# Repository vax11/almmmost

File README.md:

# Almmmost

Almmmost is a reimplementation of TeleVideo, Inc's MmmOST network operating
system, which provided a small business network to a set of Z80 or 8088-based
TeleVideo computers in the early 1980s.

Almmmost reimplements the core functions of file and disk sharing, along with
"special file" handling, which allows programs to interact with the server to
request dynamic data, or data from other sources.

The hardware part of Almmmost depends on a Next Thing Co. CHIP single board
computer, and a custom GPIO interface to a Zilog Z85C30 serial chip. This
provides an RS-422 SDLC interface running at 800K baud, for the client systems
to talk to.  A custom Linux kernel driver is provided to interface with the 
hardware, and allow easy porting to other similar single-board computers.

The kernel driver is in the "tvi\_sdlc" directory, and depends on kernel
sources to be built. If building on a NTC Chip, I recommend getting a copy
of the 4.4.138-chip kernel from here: 
https://github.com/kaplan2539/CHIP-Debian-Kernel

The needed dtb to enable the PWM, which provides the serial Tx clock, is
provided as well, and should be copied to /boot/sun5i-r8-chip.dtb

libini is required, and can be acquired from here:
https://github.com/pcercuei/libini

To compile libini, run "cmake ." in the source directory, and then the usual
make / make install.  On Debian, you'll probably first need to edit 
CMakeLists.txt to change the required cmake version to 3.0.0. I had no issues
with changing that requirement in my testing.

To build Almmmost, once you have the other things built, just cd into the 
directory and run "make".  There are a set of Z80 programs that can be built
with "z80asm" from the like named Debian/Ubuntu package.  To copy files onto
the client, you can point the "filein.sys" link to the file on the server,
and on the client just do:
```
pip a:whatever.com=b:filein.sys
```

Almmmost requires OS images for the client systems. The stock config file 
uses MmmOST 2.1 versions of the client OSes.  These are available in the
TS806 install images "tv806.zip" on Dave Dunfield's site, which will need
to be extracted from the Imagedisk images. You can use Imagedisk to convert
to a raw image, and then 22DISK, UNIFORM, or simlilar to copy the files
out. The OS images are named like "USERCPM.DAT":
http://www.classiccmp.org/dunfield/img/index.htm

To generate the binary versions of the bootloaders, you can convert the HEX
version to a binary version, doing something like this, on linux:
```
objcopy -i ihex -o binary XPDUBOOT.HEX XPDUBOOT.BIN
```

You'll next need to generate disk images. CP/M expects empty disks to
contain all e5 (hex) bytes, so I've included a program, "make\_e5.c", which
generates a stream of e5 bytes. For an 8MB image, do:
```
./make_e5 | dd of=drive_a.img bs=1M count=8
```

For floppy disk images, you can use Imagedisk images converted to raw images
on DOS:
```
IMDU /BIN BLAH.IMD BLAH.BIN
```

Running almmmost is as simple as:
```
./almmmost almmmost.ini
```

## Configuration file
almmmost.ini is an ini-format config file to set most of the parameters for
Almmmost.  A lot of it won't need to be touched to make this work, but here's
the main things you may want to modify:

```
[Device]
```
Set Ports= to the number of ports you have, and for each one (numbered 0 and up),
have a User Dev n = line pointing to the device name, and a User Port n = line
with the number of the ports on the card.  Each Z85C30 card has two ports, and
are numbered based on the board number * 2. So a board with the dip switches
set for the first select, would be ports 0 (A) and 1 (B). The second select is
ports 2 (A) and 3 (B).

```
[General]
```
This sets the MmmOST general revisison number and the disk number (0=A) for the
print spool.  Print spooling is not yet implemented.

```
[Port n]
```
This sets whether or not the client on this port number (these are based on the
numbers you set in the device section, not the physical numbers) runs an 
autologon command, and which private directory number it should use for its 
private drive.

```
[Clients]
```
This sets where the OS images and bootloaders are kept on the disk, and the
max number for the hardware type

```
[Client OSTYPE n]
```
This sets the filenames for the boot loader and OS image for each Client's 
hardware type.  This is the hardware type sent by the Boot rom to the server, 
and generally is:

```
0 = U = TS-800A, TS-801, TS-802
1 = TS-802H
2 = TS-1602
3 = TS-1603
4 = TS-803
5 = TS-803H
6 = TS-800R
7 = TPC-I
```

Values are listed for the base address that byte 0 of the OS image is loaded at,
the memory address for the Hardware Parameter Table (HPAM), and the address
of the Console Buffer (CONBUF). These are somewhat documented in almmmost\_osload.h

```
[Disks] 
```
This lists the number of drives that are presented to the client, and the
directory that they're stored in, along with the maximum private directory number

```
[Disk n]
```
This gives the disk type, image file names/rw status, and parameters for CP/M:
```
Type : either PRIVATE, PUBLIC, or PUBLIC_ONLY, matching MmmOST's definitions.
Image n : one Image is used per private directory on a disk. 0 is used for
	public/public only disks
Floppy : Y or N depending on if it's emulating a floppy disk that can be changed
SPT : CP/M Sectors per track
BSF : CP/M Block shift factor
DBM : CP/M Max data block number
DBL : Maximum directory entry number
ALx : The number of blocks reserved for the directory entries. This matches the
	number of 1 bits in AL0 / AL1
RES : The number of reserved tracks (for OS or disk partitioning)
EXM : CP/M Extent Mask
```

Most of those values are based on the CP/M Disk Paramaeter Block information to
describe a disk image. The example config gives A: as a private drive of 8MB 
(the max in CP/M 2.2), B: as a public (shared file) drive of 8MB, and C: matching
the TeleVideo 360K CP/M floppy format.

## Command interface

Pressing ^C while running will halt the server and bring up a command line,
with commands available for debugging problems, or making some changes to the
system state.  The commands are listed below:

```
abort
```

Abort the current command, useful if Almmmost is waiting for the client to 
send data, but the client is hung up for some reason.

```
locate
```
Prints out the current do/while loop that the server is in, waiting for the
client to do something.

```
reopen <Disk>[:DIR] <filename>
```

eg, reopen C /root/floppy2.img ... or reopen A:0 driveA-dir0.img
Closes the current image file, and opens a new one in its place.  You will 
want to hit ^C on the client after doing this, or it might corrupt the new 
disk.

If filename starts with a "/", it assumes an absolute path, otherwise it 
looks starting in the directory specified in the config file.

```
filein <filename>
```
Changes what file on the server is used to supply data for the "filein.sys"
special file

```
fileout <filename>
```
Changes what file on the server is written to by wiriting to the "fileout.sys"
special file.

```
closeport <n>
```
Closes all open files on port #n.  Useful if the client died, and left files
open. Ensures that data is written back to disk.

```
printfil
```
Print all open files on shared drives

```
printspe
```
Print names of all special files that are handled by Almmmost

```
printdpb
```
Print the CP/M Drive Parameter Blocks that were generated by Almmmost for the
disk images.

```
printhpb
```
Print the Hardware Parameter Blocks that were generated by Almmmost based on
the config file values, for each hardware type

```
saveos <filename>
```
Saves the modified OS image, with the generated HPB/DPH/DPBs that were inserted
into it

```
sync
```
Save all open files on shared drives to the image in their current state 
(makes sure directory entries are saved)

```
exit
quit
```
Runs "sync", and then exits Almmmost.

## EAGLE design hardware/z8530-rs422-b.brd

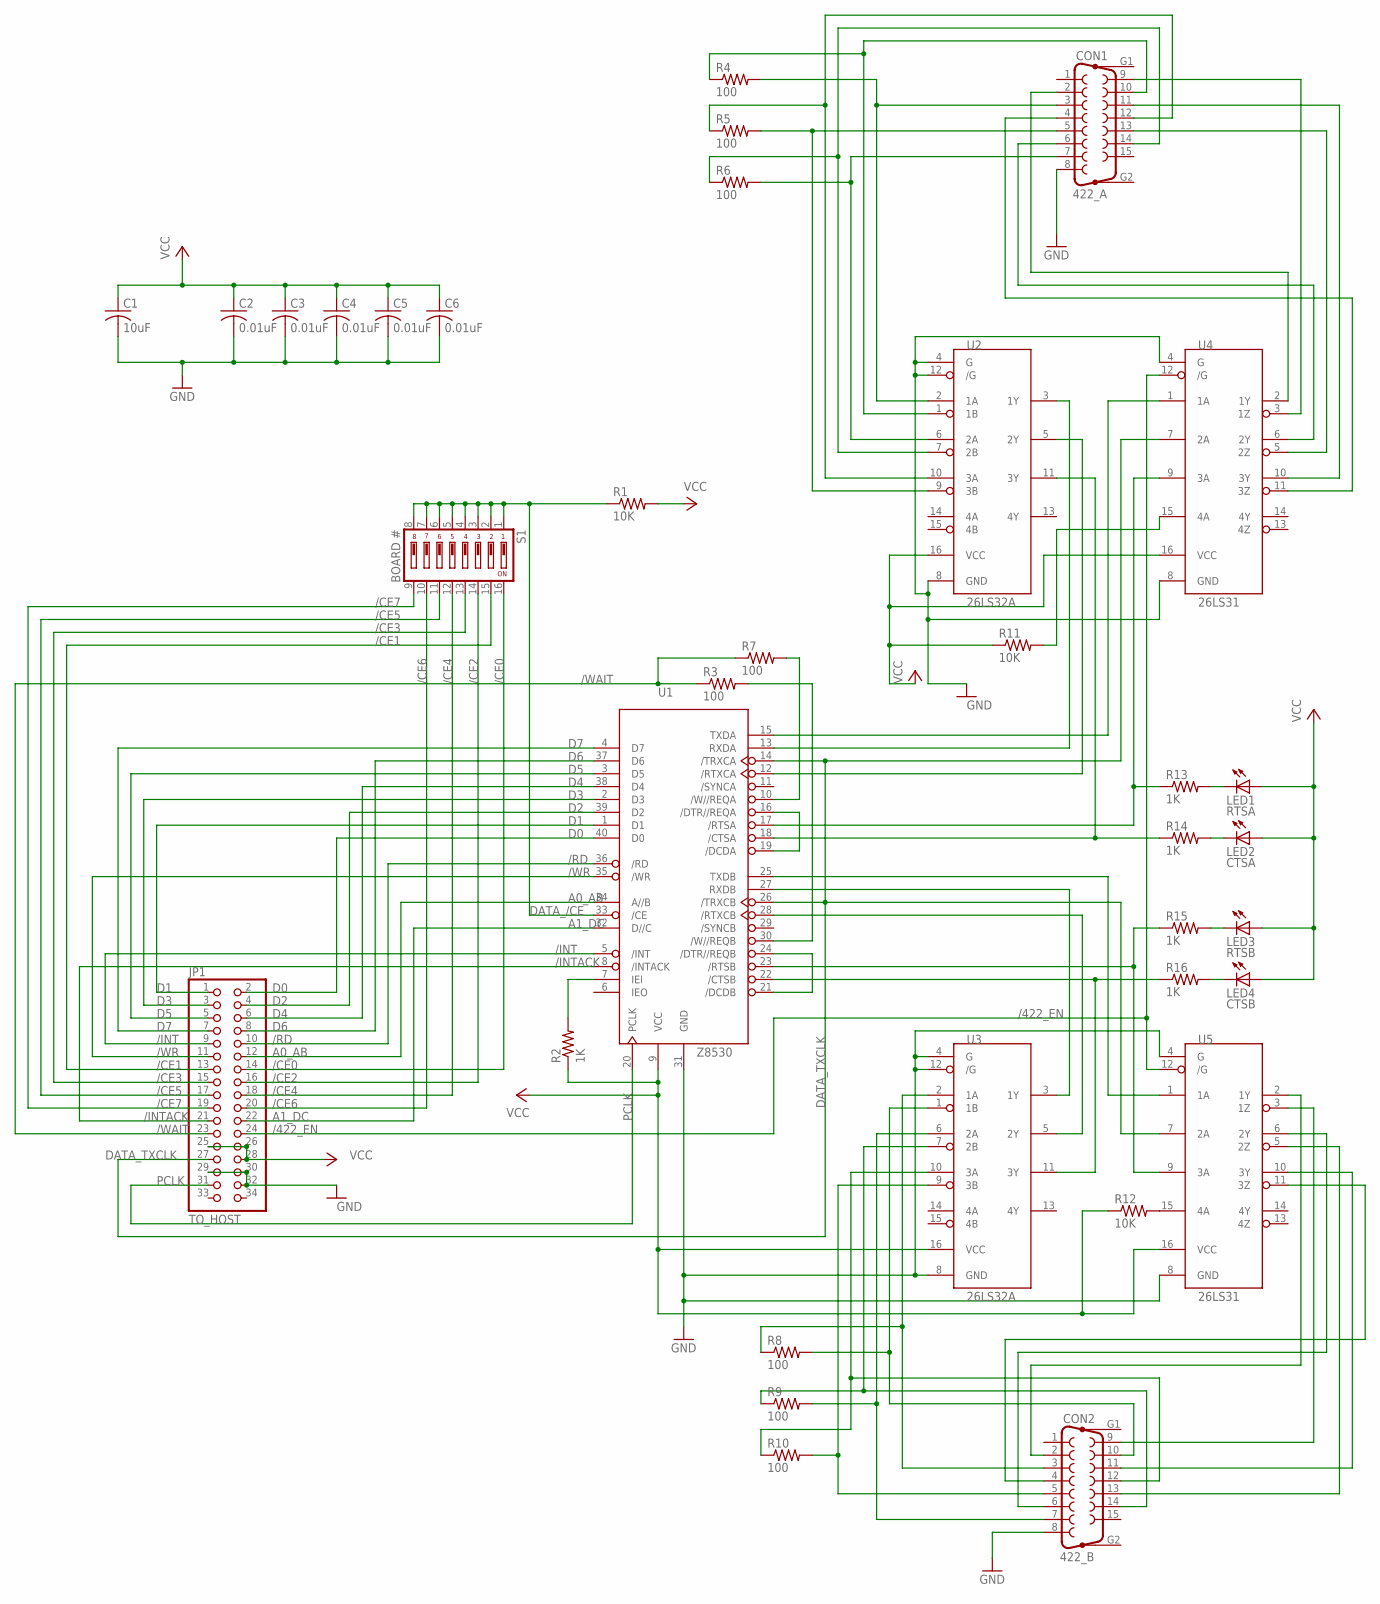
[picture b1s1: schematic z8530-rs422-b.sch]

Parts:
C1: 10uF; C0805
C2, C3, C4, C5, C6: 0.01uF; C0805
CON1: 422_A; F15VP
CON2: 422_B; F15VP
JP1: TO_HOST; 2X17
LED1: RTSA; LED3MM
LED2: CTSA; LED3MM
LED3: RTSB; LED3MM
LED4: CTSB; LED3MM
R1, R11, R12: 10K; R0805
R2, R13, R14, R15, R16: 1K; R0805
R3, R4, R5, R6, R7, R8, R9, R10: 100; R0805
S1: BOARD #; DP-08
U1: Z8530; DIL40
U2, U3: 26LS32A; DIP16
U4, U5: 26LS31; DIP16

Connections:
/422_EN: JP1.24, U4.12 (/G), U5.12 (/G)
/CE0: JP1.14, S1.16
/CE1: JP1.13, S1.15
/CE2: JP1.16, S1.14
/CE3: JP1.15, S1.13
/CE4: JP1.18, S1.12
/CE5: JP1.17, S1.11
/CE6: JP1.20, S1.10
/CE7: JP1.19, S1.9
/INT: JP1.9, U1.5 (/INT)
/INTACK: JP1.21, U1.8 (/INTACK)
/RD: JP1.10, U1.36 (/RD)
/WAIT: JP1.23, R3.1, R7.1
/WR: JP1.11, U1.35 (/WR)
A0_AB: JP1.12, U1.34 (A//B)
A1_DC: JP1.22, U1.32 (D//C)
D0: JP1.2, U1.40 (D0)
D1: JP1.1, U1.1 (D1)
D2: JP1.4, U1.39 (D2)
D3: JP1.3, U1.2 (D3)
D4: JP1.6, U1.38 (D4)
D5: JP1.5, U1.3 (D5)
D6: JP1.8, U1.37 (D6)
D7: JP1.7, U1.4 (D7)
DATA_/CE: R1.1, S1.1, S1.2, S1.3, S1.4, S1.5, S1.6, S1.7, S1.8, U1.33 (/CE)
DATA_TXCLK: JP1.27, U1.14 (/TRXCA), U1.26 (/TRXCB), U4.7 (2A), U5.7 (2A)
GND: C1.2, C2.2, C3.2, C4.2, C5.2, C6.2, CON1.8, CON2.8, JP1.29, JP1.30, JP1.32, U1.31 (GND), U2.4 (G), U2.8 (GND), U2.12 (/G), U3.4 (G), U3.8 (GND), U3.12 (/G), U4.4 (G), U4.8 (GND), U5.4 (G), U5.8 (GND)
unnamed: R7.2, U1.10 (/W//REQA)
unnamed: R3.2, U1.30 (/W//REQB)
unnamed: U1.13 (RXDA), U2.3 (1Y)
unnamed: U1.12 (/RTXCA), U2.5 (2Y)
unnamed: R14.1, U1.18 (/CTSA), U2.11 (3Y)
unnamed: U1.15 (TXDA), U4.1 (1A)
unnamed: R13.1, U1.17 (/RTSA), U4.9 (3A)
unnamed: U1.16 (/DTR//REQA), U1.19 (/DCDA)
unnamed: U1.21 (/DCDB), U1.24 (/DTR//REQB)
unnamed: U1.27 (RXDB), U3.3 (1Y)
unnamed: U1.28 (/RTXCB), U3.5 (2Y)
unnamed: R16.1, U1.22 (/CTSB), U3.11 (3Y)
unnamed: U1.25 (TXDB), U5.1 (1A)
unnamed: R15.1, U1.23 (/RTSB), U5.9 (3A)
unnamed: CON1.3, R4.2, U2.2 (1A)
unnamed: CON1.10, R4.1, U2.1 (1B)
unnamed: CON1.7, R6.2, U2.6 (2A)
unnamed: CON1.14, R6.1, U2.7 (2B)
unnamed: CON1.12, R5.1, U2.10 (3A)
unnamed: CON1.5, R5.2, U2.9 (3B)
unnamed: CON1.2, U4.2 (1Y)
unnamed: CON1.9, U4.3 (1Z)
unnamed: CON1.6, U4.6 (2Y)
unnamed: CON1.13, U4.5 (2Z)
unnamed: CON1.11, U4.10 (3Y)
unnamed: CON1.4, U4.11 (3Z)
unnamed: CON2.3, R8.1, U3.2 (1A)
unnamed: CON2.10, R8.2, U3.1 (1B)
unnamed: CON2.7, R9.2, U3.6 (2A)
unnamed: CON2.14, R9.1, U3.7 (2B)
unnamed: CON2.12, R10.1, U3.10 (3A)
unnamed: CON2.5, R10.2, U3.9 (3B)
unnamed: CON2.2, U5.2 (1Y)
unnamed: CON2.9, U5.3 (1Z)
unnamed: CON2.6, U5.6 (2Y)
unnamed: CON2.13, U5.5 (2Z)
unnamed: CON2.11, U5.10 (3Y)
unnamed: CON2.4, U5.11 (3Z)
unnamed: LED1.K (C), R13.2
unnamed: LED3.K (C), R15.2
unnamed: LED2.K (C), R14.2
unnamed: LED4.K (C), R16.2
unnamed: R2.2, U1.7 (IEI)
unnamed: R11.2, U4.15 (4A)
unnamed: R12.2, U5.15 (4A)
PCLK: JP1.31, U1.20 (PCLK)
VCC: C1.1, C2.1, C3.1, C4.1, C5.1, C6.1, JP1.25, JP1.26, JP1.28, LED1.A, LED2.A, LED3.A, LED4.A, R1.2, R2.1, R11.1, R12.1, U1.9 (VCC), U2.16 (VCC), U3.16 (VCC), U4.16 (VCC), U5.16 (VCC)

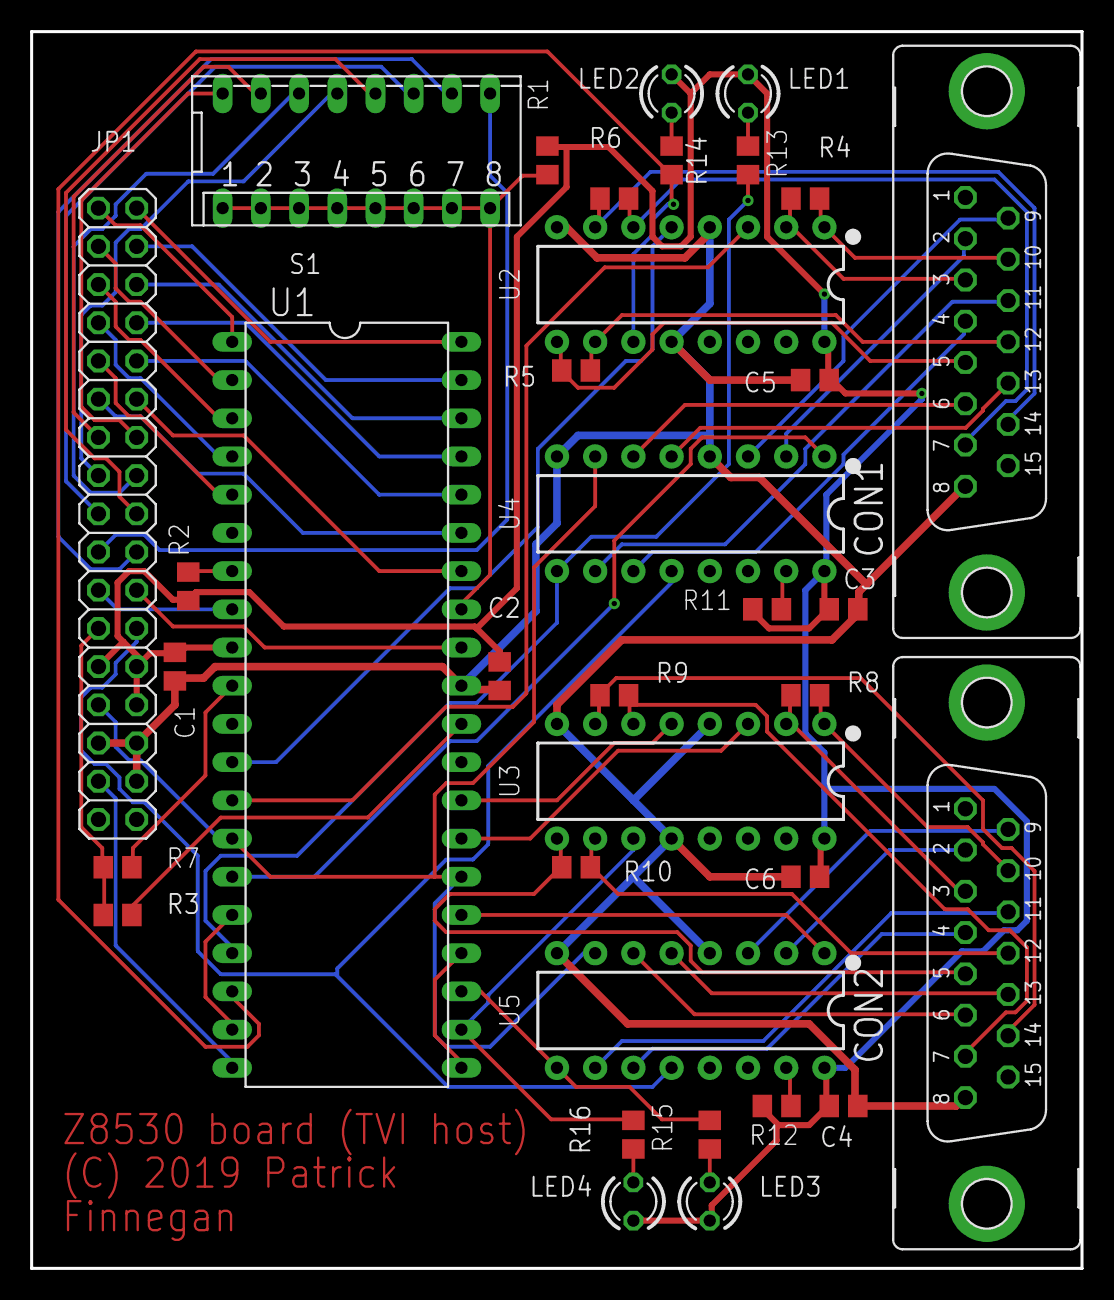
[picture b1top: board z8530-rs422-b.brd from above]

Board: 2 copper layers, 69.8 x 82.2 mm, 35 parts (0 on the bottom side), 74 nets.

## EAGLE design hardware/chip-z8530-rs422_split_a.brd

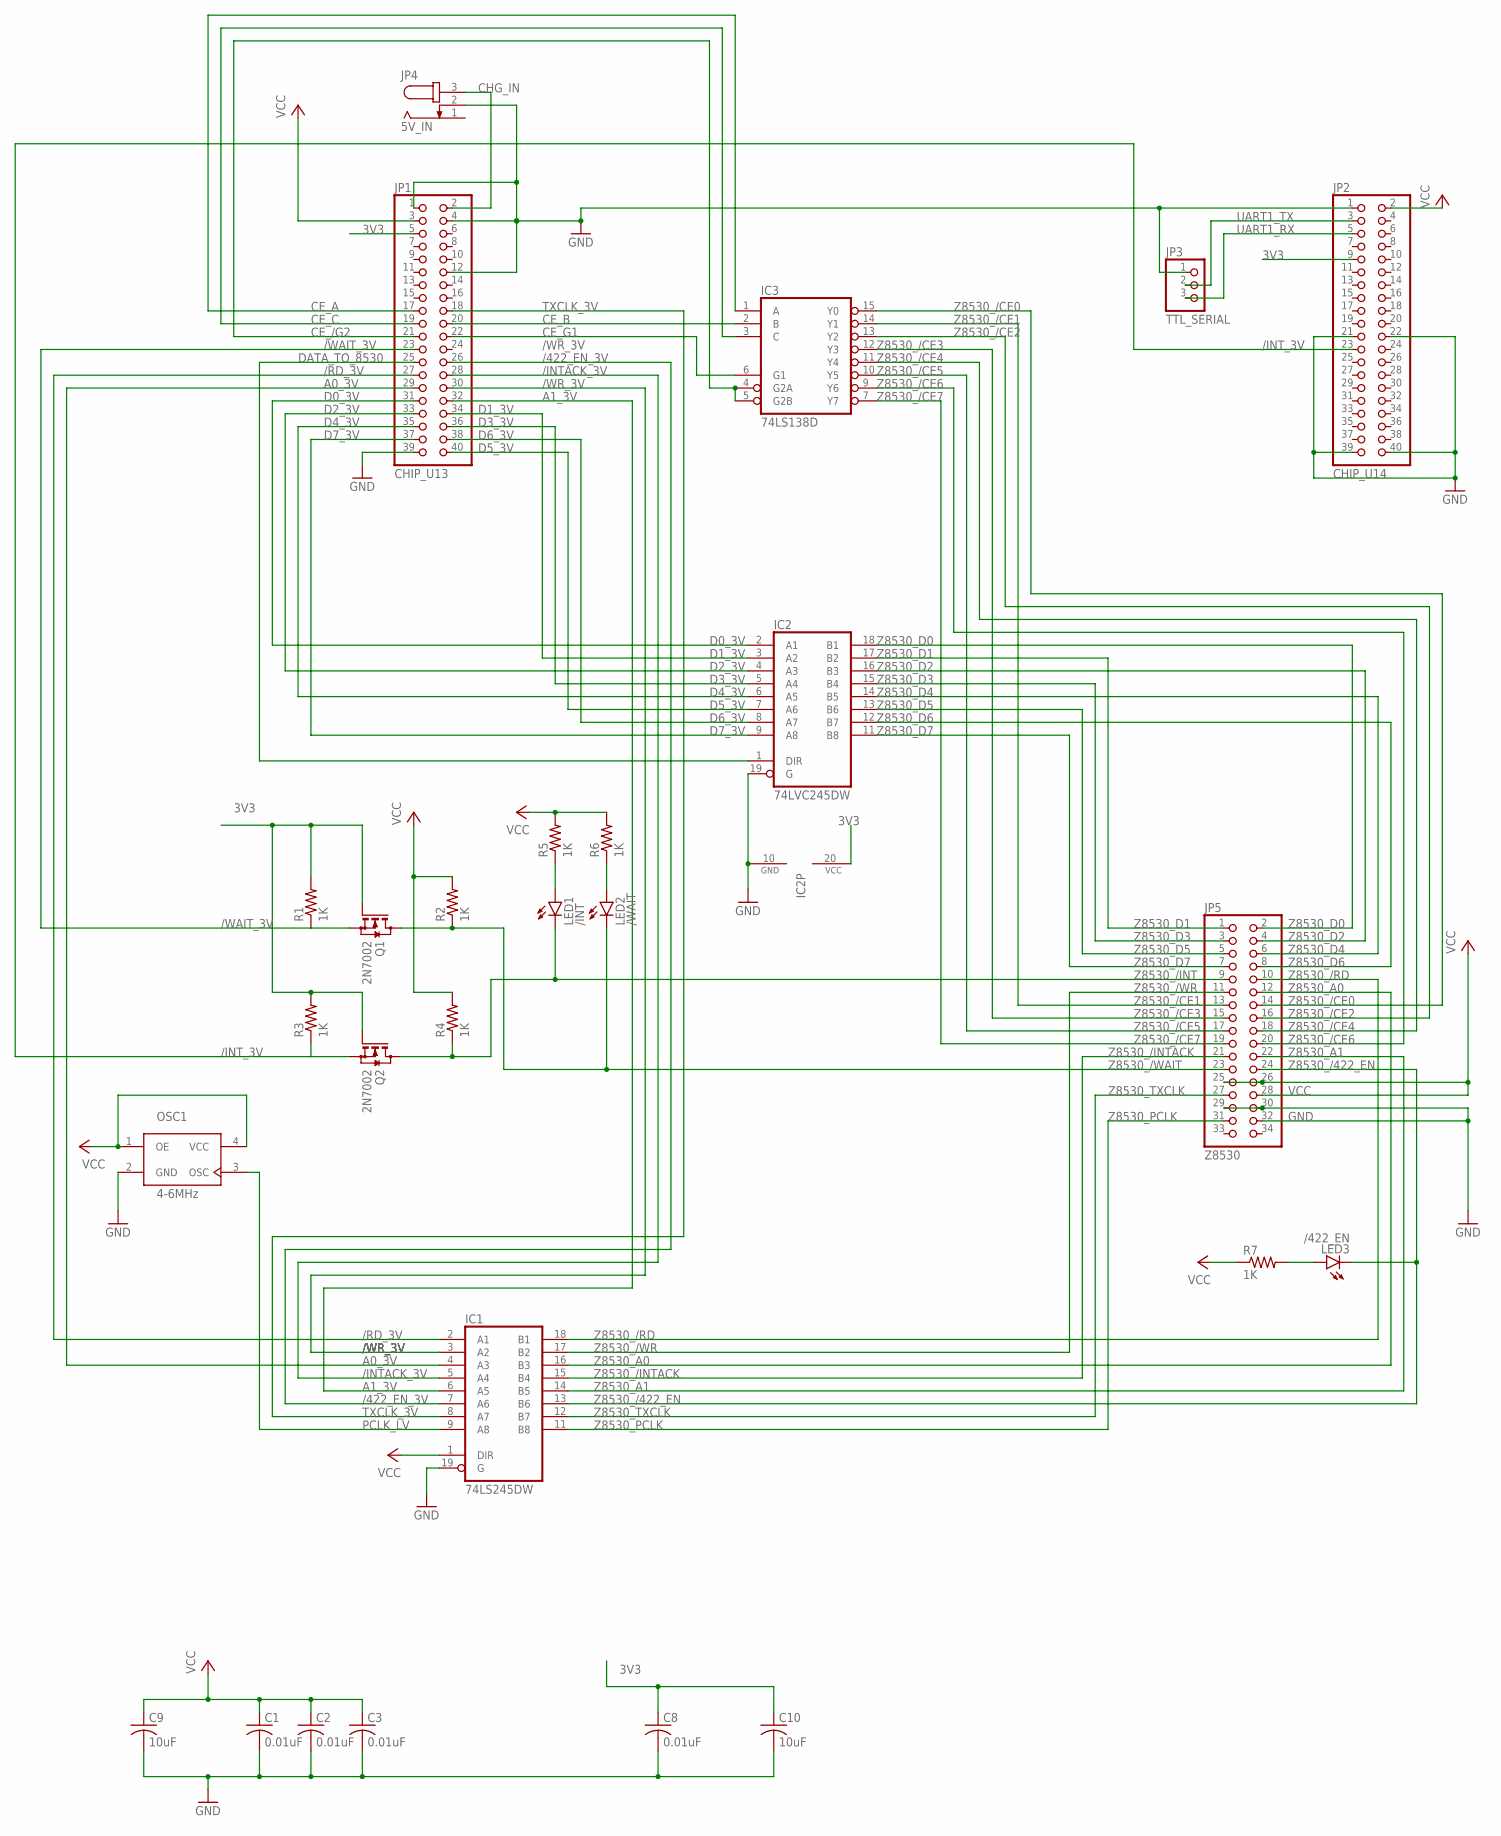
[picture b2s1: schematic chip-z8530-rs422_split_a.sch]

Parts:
C1, C2, C3, C8: 0.01uF; C0805
C9, C10: 10uF; C0805
IC1: 74LS245DW; SO20W
IC2: 74LVC245DW; SO20W
IC3: 74LS138D; SO16
JP1: CHIP_U13; 2X20
JP2: CHIP_U14; 2X20
JP3: TTL_SERIAL; 1X03/90
JP4: 5V_IN; SPC4078
JP5: Z8530; 2X17
LED1: /INT; LED3MM
LED2: /WAIT; LED3MM
LED3: /422_EN; LED3MM
OSC1: 4-6MHz; SG5032
Q1, Q2: 2N7002; SOT23
R1, R2, R3, R4, R5, R6, R7: 1K; R0805

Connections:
3V3: C8.1, C10.1, IC2.20 (VCC), JP1.5, JP2.9, Q1.1 (G), Q2.1 (G), R1.2, R3.2
/422_EN_3V: IC1.7 (A6), JP1.26
/INTACK_3V: IC1.5 (A4), JP1.28
/INT_3V: JP2.23, Q2.2 (S), R3.1
/RD_3V: IC1.2 (A1), JP1.27
/WAIT_3V: JP1.23, Q1.2 (S), R1.1
/WR_3V: IC1.3 (A2), JP1.30
A0_3V: IC1.4 (A3), JP1.29
A1_3V: IC1.6 (A5), JP1.32
CE_/G2: IC3.4 (G2A), IC3.5 (G2B), JP1.21
CE_A: IC3.1 (A), JP1.17
CE_B: IC3.2 (B), JP1.20
CE_C: IC3.3 (C), JP1.19
CE_G1: IC3.6 (G1), JP1.22
CHG_IN: JP1.2, JP4.3
D0_3V: IC2.2 (A1), JP1.31
D1_3V: IC2.3 (A2), JP1.34
D2_3V: IC2.4 (A3), JP1.33
D3_3V: IC2.5 (A4), JP1.36
D4_3V: IC2.6 (A5), JP1.35
D5_3V: IC2.7 (A6), JP1.40
D6_3V: IC2.8 (A7), JP1.38
D7_3V: IC2.9 (A8), JP1.37
DATA_TO_8530: IC2.1 (DIR), JP1.25
GND: C1.2, C2.2, C3.2, C8.2, C9.2, C10.2, IC1.10 (GND), IC1.19 (G), IC2.10 (GND), IC2.19 (G), IC3.8 (GND), JP1.1, JP1.4, JP1.12, JP1.39, JP2.1, JP2.21, JP2.22, JP2.39, JP2.40, JP3.1, JP4.2, JP5.29, JP5.30, JP5.32, OSC1.2 (GND)
unnamed: LED1.A, R5.1
unnamed: LED2.A, R6.1
unnamed: LED3.A, R7.2
PCLK_LV: IC1.9 (A8), OSC1.3 (OSC)
TXCLK_3V: IC1.8 (A7), JP1.18
UART1_RX: JP2.5, JP3.3
UART1_TX: JP2.3, JP3.2
VCC: C1.1, C2.1, C3.1, C9.1, IC1.1 (DIR), IC1.20 (VCC), IC3.16 (VCC), JP1.3, JP2.2, JP5.25, JP5.26, JP5.28, OSC1.1 (OE), OSC1.4 (VCC), R2.2, R4.2, R5.2, R6.2, R7.1
Z8530_/422_EN: IC1.13 (B6), JP5.24, LED3.K (C)
Z8530_/CE0: IC3.15 (Y0), JP5.14
Z8530_/CE1: IC3.14 (Y1), JP5.13
Z8530_/CE2: IC3.13 (Y2), JP5.16
Z8530_/CE3: IC3.12 (Y3), JP5.15
Z8530_/CE4: IC3.11 (Y4), JP5.18
Z8530_/CE5: IC3.10 (Y5), JP5.17
Z8530_/CE6: IC3.9 (Y6), JP5.20
Z8530_/CE7: IC3.7 (Y7), JP5.19
Z8530_/INT: JP5.9, LED1.K (C), Q2.3 (D), R4.1
Z8530_/INTACK: IC1.15 (B4), JP5.21
Z8530_/RD: IC1.18 (B1), JP5.10
Z8530_/WAIT: JP5.23, LED2.K (C), Q1.3 (D), R2.1
Z8530_/WR: IC1.17 (B2), JP5.11
Z8530_A0: IC1.16 (B3), JP5.12
Z8530_A1: IC1.14 (B5), JP5.22
Z8530_D0: IC2.18 (B1), JP5.2
Z8530_D1: IC2.17 (B2), JP5.1
Z8530_D2: IC2.16 (B3), JP5.4
Z8530_D3: IC2.15 (B4), JP5.3
Z8530_D4: IC2.14 (B5), JP5.6
Z8530_D5: IC2.13 (B6), JP5.5
Z8530_D6: IC2.12 (B7), JP5.8
Z8530_D7: IC2.11 (B8), JP5.7
Z8530_PCLK: IC1.11 (B8), JP5.31
Z8530_TXCLK: IC1.12 (B7), JP5.27

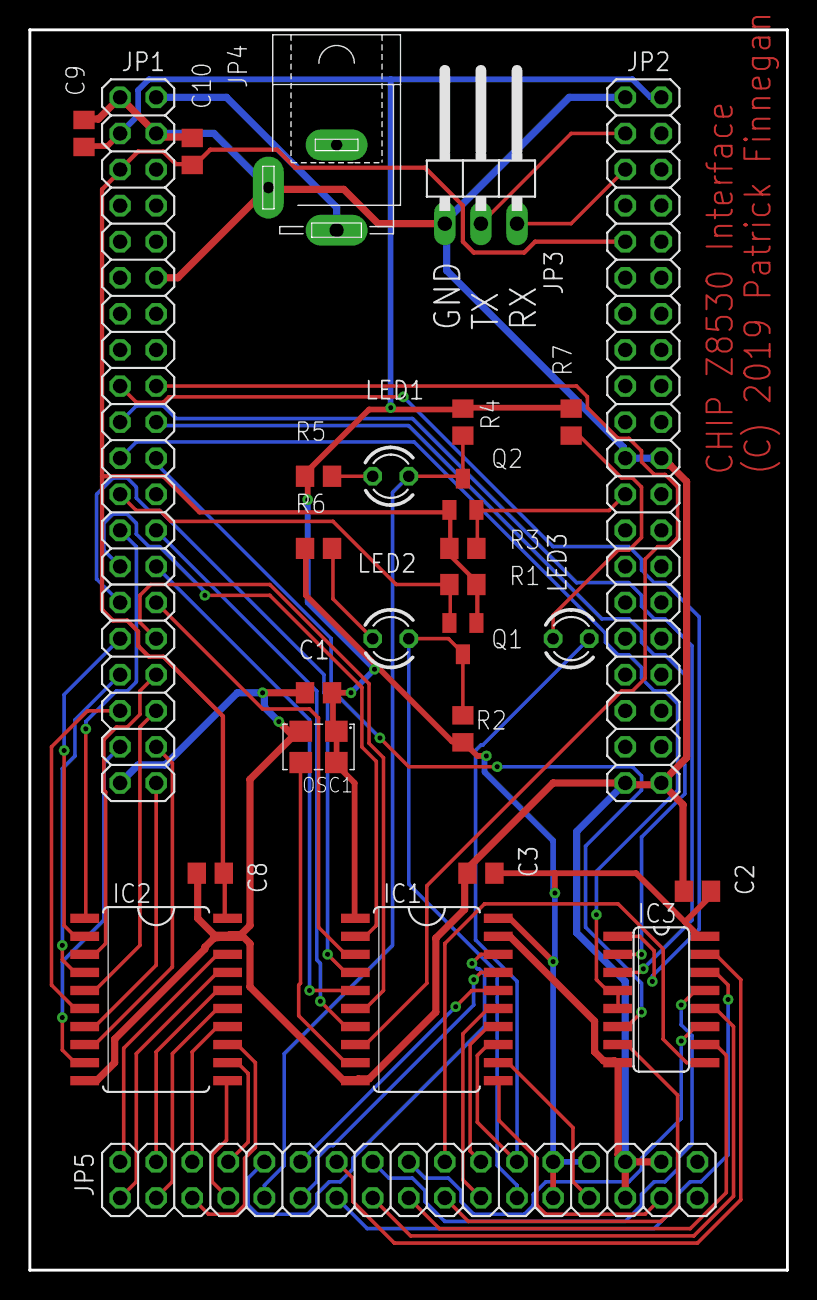
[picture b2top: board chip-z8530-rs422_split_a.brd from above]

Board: 2 copper layers, 53.3 x 87.3 mm, 27 parts (0 on the bottom side), 59 nets.

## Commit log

2019-04-19 Document Almmmost
2019-04-19 Initial import of sources
2019-04-19 Update formatting
2019-04-19 Update formatting some more
2019-04-19 Add hardware design
2019-04-22 Clean up Almmmost, and add the cgi programs

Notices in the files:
hardware/chip-z8530-rs422_split_a.brd:
(C) 2019 Patrick Finnegan
